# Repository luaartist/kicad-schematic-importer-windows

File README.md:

# KiCad Schematic Importer Plugin

A powerful KiCad plugin that uses computer vision to convert images of schematics into editable KiCad projects. Perfect for digitizing hand-drawn circuits, photographed schematics, or legacy documentation.

## Features

- Import schematics from various image formats (PNG, JPG, SVG)
- Automatic component detection
- Connection tracing
- Export to KiCad schematic format

## Installation

### Automatic Installation

Run the installation script:

```bash
python install.py --kicad-version 9.0
```

### Manual Installation

1. Copy the plugin files to the KiCad plugins directory:
   - Windows (KiCad 9.0): `%USERPROFILE%\Documents\KiCad\9.0\3rdparty\plugins\schematic_importer`
   - Windows (KiCad 7.0): `%APPDATA%\kicad\7.0\scripting\plugins\schematic_importer`
   - Linux: `~/.local/share/kicad/[version]/scripting/plugins/schematic_importer`
   - macOS: `~/Library/Application Support/kicad/[version]/scripting/plugins/schematic_importer`

2. Restart KiCad

## Usage

1. Open KiCad PCB Editor
2. Click on the "Schematic Importer" plugin in the External Plugins menu
3. Select an image file containing a schematic
4. The plugin will vectorize the image and import it into the board

## Requirements

- KiCad 7.0 or later
- Python 3.6 or later
- OpenCV (for image processing)
- wxPython (for UI)

## Development

### Project Structure

```
schematic_importer/
├── __init__.py                  # Package initialization
├── action_plugin.py             # Main plugin file
├── metadata.json                # Plugin metadata
├── resources/
│   ├── icons/
│   │   └── icon.png             # Plugin icon
│   └── templates/
├── src/
│   ├── core/
│   │   └── schematic_importer.py # Core functionality
│   ├── ui/
│   │   └── import_dialog.py     # UI components
│   └── utils/
│       ├── image_processor.py   # Image processing utilities
│       └── path_validator.py    # Path validation utilities
└── tests/
    ├── test_image_processor.py
    ├── test_path_validator.py
    └── test_schematic_importer.py
```

### Running Tests

```bash
python -m pytest
```

## License

MIT License

## Author

Wallace Lebrun - Lead Developer and Architect

## Acknowledgments

This plugin was developed using a hybrid AI-assisted development methodology, utilizing various AI platforms including:
- OpenAI ChatGPT Pro
- Anthropic Claude
- NinjaTech AI

## Contributing

Contributions are welcome! Please see the [CONTRIBUTING.md](CONTRIBUTING.md) file for guidelines.

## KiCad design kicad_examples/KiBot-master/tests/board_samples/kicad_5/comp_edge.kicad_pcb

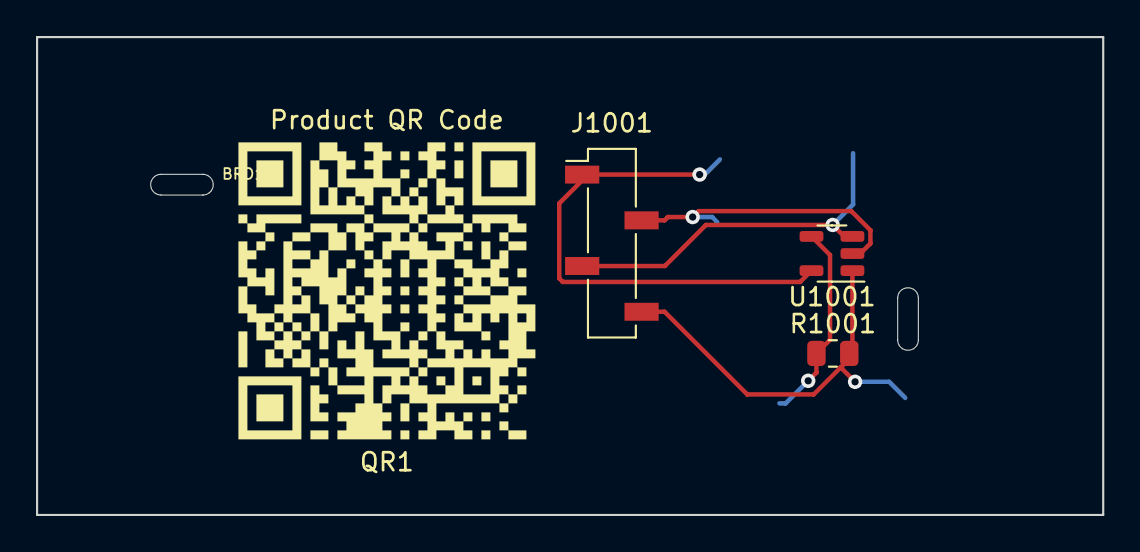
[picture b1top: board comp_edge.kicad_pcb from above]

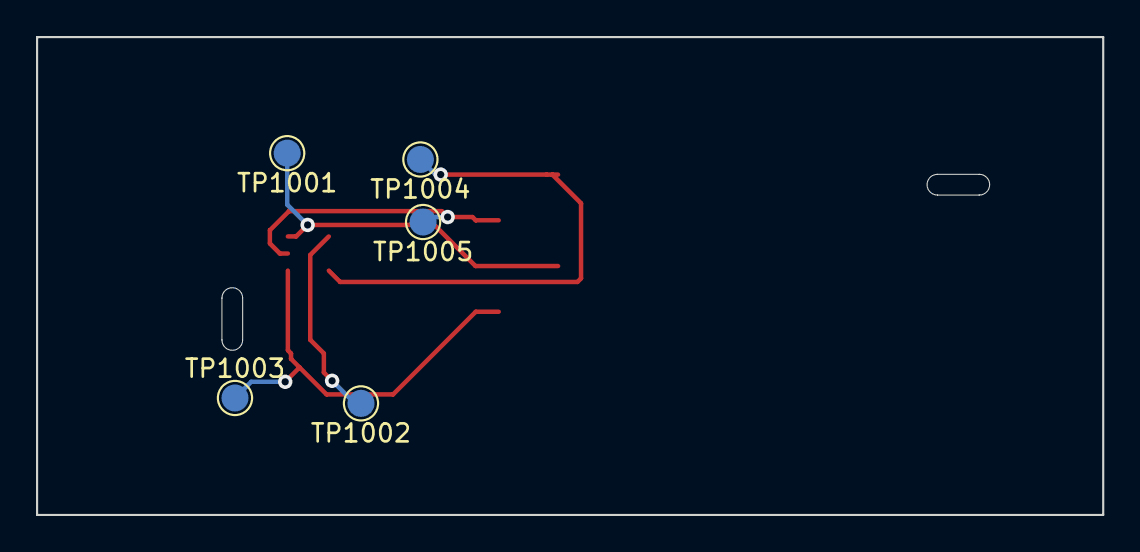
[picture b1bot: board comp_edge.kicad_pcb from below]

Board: 2 copper layers, 59.2 x 26.5 mm, 10 parts (5 on the bottom side), 5 nets.

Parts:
BRD1: SYM_Arrow_XLarge; DemoBoard
J1001: SSM-104-L-SV; PinSocket_1x04_P2.54mm_Vertical_SMD_Pin1Left
QR1: Product QR Code; TC5
R1001: 10k; R_0805_2012Metric
TP1001: TP_IN; TestPoint_Pad_D1.5mm
TP1002: TP_NEG; TestPoint_Pad_D1.5mm
TP1003: TP_OUT; TestPoint_Pad_D1.5mm
TP1004: TP_VCC; TestPoint_Pad_D1.5mm
TP1005: TP_GND; TestPoint_Pad_D1.5mm
U1001: MCP6001-OT; SOT-23-5

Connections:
/IN: J1001.3, TP1001.1, U1001.3
/OUT: J1001.4, R1001.2, TP1003.1, U1001.1
/_AOPIN+: R1001.1, TP1002.1, U1001.4
GND: J1001.2, TP1005.1, U1001.2
VCC: J1001.1, TP1004.1, U1001.5

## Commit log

2025-02-27 pdated to be Windows-only
    Commented out Linux-specific sudo apt-get commands in .github/workflows/ci.yml.
    Updated fix_file_structure.py to use Python's os.makedirs() for directory creation, ensuring compatibility with Windows.
    Modified .github/workflows/ci.yml.bak2.yml to use Windows-compatible commands for creating directories and files.
2025-02-27 Upgrading plugin modified: .github/workflows/ci.yml modified: .vscode/settings.json modified: __init__.py new file: run_windows_tests.ps1 modified: src/core/schematic_importer.py modified: src/integr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
2025-02-27 update to windows only
2025-02-27 updates
    Fixed import errors in test_import.py:
    Updated the import path to correctly import from src.core.project_manager
    Converted the file to a proper pytest test file with test functions
    Fixed requirements files:
    Removed duplicate entries in requirements-dev.txt
    Added necessary dependencies to requirements.txt (opencv-python, numpy, pillow, python-potrace)
2025-02-27 update
    Fixed dependency issues:
    Installed Pillow (PIL) which was missing
    Added a fallback mechanism for python-potrace since it wasn't available
    Fixed import structure problems:
    Reverted __init__.py to use absolute imports instead of relative imports
    Updated test files to use direct imports
2025-02-27 implemented alternative vectorization option
    Installed and integrated multiple alternative vectorization libraries:
    autotrace: A command-line tool for converting bitmap images to vector graphics
    svgpathtools: A Python library for SVG path manipulation and creation
    opencv-python: A computer vision library with contour detection capabilities
    Created a new AlternativeImageProcessor class that:
    Provides the same interface as the original ImageProcessor
2025-02-27 added svgpathtools
    update
2025-02-27 fix: normalize Windows path comparisons in tests
    - Add os.path.normcase() to path assertions in test files
    - Handle Windows short path (8.3) vs long path comparisons
    - Update mock paths to use Windows-style paths
    - Fix path comparison issues in image processor tests
    This fixes test failures caused by path format mismatches between
    C:\Users\RUNNER~1 and C:\Users\runneradmin on Windows CI environments.
2025-02-27 fix: improve subprocess security and input validation
    Address Bandit security warnings (B404, B603) related to subprocess usage:
    - Add strict path validation to prevent path traversal
    - Implement secure subprocess execution with shell=False
    - Add allowlist for external tools (inkscape, potrace, autotrace)
    - Improve error handling and input sanitization
    - Add timeout parameter to prevent hanging processes
2025-02-27 feat(coverage): Enable apply mode in coverage configuration
    - Add apply=true to [run] and [xml] sections
    - Ensure coverage settings are actively applied during test execution
    - Maintain existing exclusion patterns and source paths
    - Improve XML report generation configuration
    This change ensures more accurate coverage reporting by explicitly enabling
    the apply mode, which enforces coverage configuration during test runs and
2025-02-27 fix: improve subprocess security and address Bandit warnings
    Implements comprehensive path validation and security checks to address
    Bandit B404 and B603 warnings while maintaining functionality:
    - Add PathValidator class for centralized security checks
    - Validate executable paths are in safe system directories
    - Restrict output paths to project or temp directories
    - Add documented nosec comments for safe subprocess usage
2025-02-27 fix: resolve CI failures and security warnings
    - Add PathValidator class for secure path handling
    - Fix subprocess security warnings (Bandit B603)
    - Replace hardcoded temp directory with tempfile.gettempdir()
    - Make skidl dependency Windows-specific
    - Improve CI workflow timeouts
    Technical changes:
2025-02-27 update
    Updated actions/checkout from v3 to v4 to match other workflow files
    Updated Python version to 3.10 to maintain consistency with other workflows
    Added setuptools and wheel to pip upgrades
    Added flake8 linting step that matches other workflows
    Added verbose test output with -v flag
    Updated codecov-action to v4 and added required token configuration
2025-02-27 Update test_alternative_image_processor.py
    Fixed the tool mocking to use AutoTrace for convert_to_svg and Inkscape for _vectorize_with_inkscape
    Added proper path argument to all lambda functions used in side_effect
    Added proper file existence checks that distinguish between input (.png) and output (.svg) files
    Updated error messages to match the actual code
    Made the mock behavior more explicit with separate functions for different test scenarios
2025-02-27 Update test_alternative_image_processor.py
    update
2025-02-27 Update schematic_importer.py
    update
2025-02-27 Update security.yml
    update
2025-02-27 update
    update
2025-02-27 Rename ci.yml.bak2.yml to ci.yml.bak
2025-02-27 window setup
2025-02-27 update1
2025-02-27 update2
2025-02-27 update 4
2025-02-28 git add . && git commit -m "test: Fix pytest failures and improve testing infrastructure
    - Add mock pcbnew module for testing without KiCad installation
    - Update conftest.py to use mock pcbnew module
    - Add test_plugin.py to verify mock pcbnew functionality
    - Add test_install_advanced_plugin.py for installer tests
    - Fix string formatting in install_advanced_plugin.py
    - Add board state management in tests
2025-02-28 fix: Resolve string formatting issues in installer
    - Create fixed v2 version of installer with proper string handling
    - Replace triple-quoted string with string concatenation
    - Update tests to use fixed v2 version
    - Fix icon file path formatting
    - Add proper test fixtures and mocking
    - Add board state management in tests
2025-02-28 ci: add .deepsource.toml
2025-02-28 feat: Add component recognition and connection tracing
    - Add ComponentRecognizer class for identifying electronic components
    - Add ConnectionTracer class for tracing connections between components
    - Add unit tests for component recognition and connection tracing
    - Fix import paths in tests
    - Add test image generation and cleanup
    - Add component type detection based on aspect ratios
2025-02-28 update
    -added image processing diagnostics to help debug the image processing pipeline
    -add a test for the image processor to verify the debug output
    -
2025-02-28 - Add file hash verification to ensure unique processing - Add debug directory for intermediate outputs - Add thumbnail generation for visual verification - Add detailed logging of image statistics -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
    - Add file hash verification to ensure unique processing
    - Add debug directory for intermediate outputs
    - Add thumbnail generation for visual verification
    - Add detailed logging of i
2025-02-28 Rename codacy-fixes.txt to codacy-fixes,patch
2025-02-28 Update dependencies and fix NumPy installation
